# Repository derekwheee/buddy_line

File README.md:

# Line Buddy

A breadboard friend for prototyping with line level audio output

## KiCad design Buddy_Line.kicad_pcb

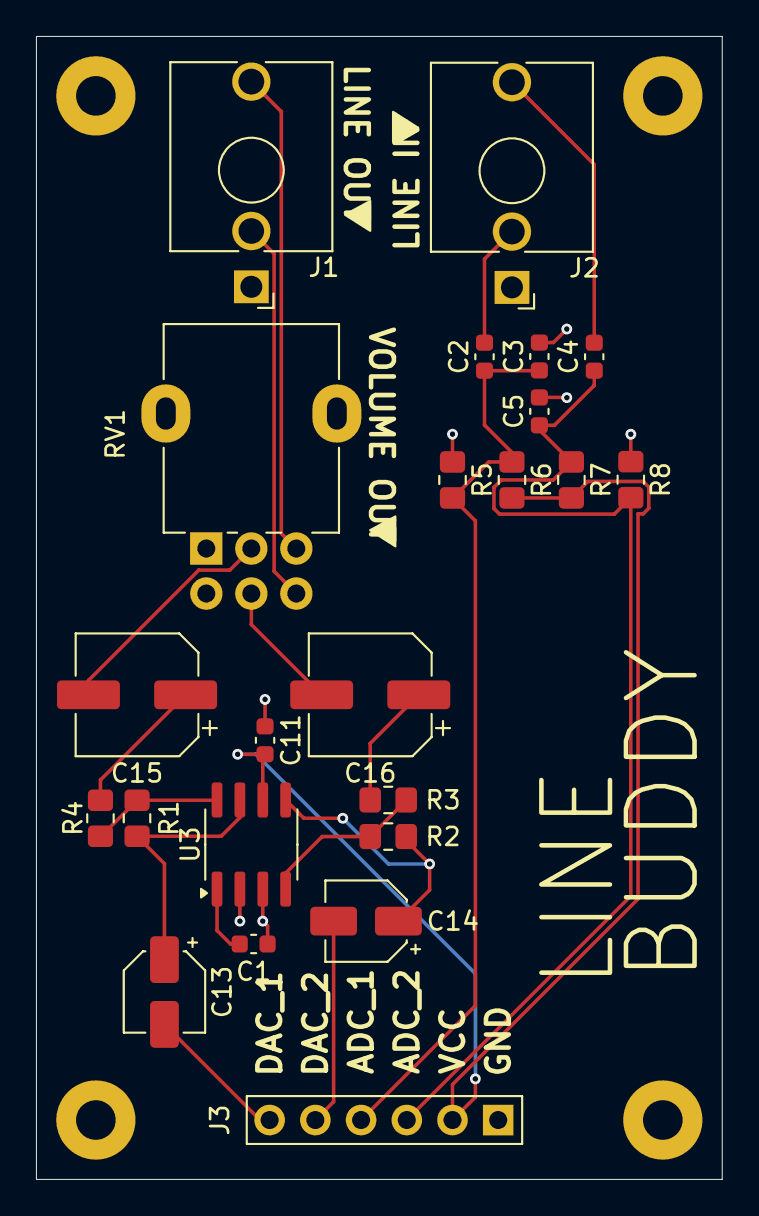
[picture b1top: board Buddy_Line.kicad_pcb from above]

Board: 2 copper layers, 38.1 x 63.5 mm, 27 parts (0 on the bottom side), 12 nets.

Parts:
C1, C3, C5, C11: 0.1u; C_0603_1608Metric
C2, C4: 10u; C_0603_1608Metric
C13, C14: 1u; CP_Elec_4x5.4
C15, C16: 68u; CP_Elec_6.3x7.7
H1, H2, H3, H4: MountingHole_Pad; MountingHole_2.2mm_M2_Pad
J1, J2: AudioJack3; Jack_3.5mm_QingPu_WQP-PJ398SM_Vertical_CircularHoles
J3: Conn_01x06_Pin; PinSocket_1x06_P2.54mm_Vertical
R1, R2: 33K; R_0805_2012Metric_Pad1.20x1.40mm_HandSolder
R3, R4: 22K; R_0805_2012Metric_Pad1.20x1.40mm_HandSolder
R5, R6, R7, R8: 1K; R_0805_2012Metric_Pad1.20x1.40mm_HandSolder
RV1: R_Potentiometer_Dual; Potentiometer_Alpha_RD902F-40-00D_Dual_Vertical
U3: TPA6110A2DGN; SOIC-8_3.9x4.9mm_P1.27mm

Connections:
+3.3V: C11.2, J3.5, R6.2, R7.2, U3.6 (VDD)
ADC_1: C2.1, C3.1, J3.3, R5.2, R6.1
ADC_2: C4.1, C5.1, J3.4, R7.1, R8.2
DAC_1: C13.2, J3.1
DAC_2: C14.2, J3.2
GND: C1.2, C3.2, C5.2, C11.1, H1.1, H2.1, H3.1, H4.1, J1.S, J2.S, J3.6, R5.1, R8.1, RV1.1, RV1.4, U3.2 (GND), U3.3 (SHDN)
unnamed: C2.2, J2.TN
unnamed: C4.2, J2.T
unnamed: J1.T, RV1.3
unnamed: J1.TN, RV1.6
unnamed: R1.2, R4.2, U3.8 (IN1-)
unnamed: R2.1, R3.2, U3.4 (IN2-)

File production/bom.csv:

Designator,Footprint,Quantity,Value,LCSC Part #
C1,0603,1,0.1u,
"C11, C3, C5",0603,3,0.1u,C6666325
"C13, C14",CP_Elec_4x5.4,2,1u,C3001203
"C15, C16",CP_Elec_6.3x7.7,2,68u,C5221836
"C2, C4",0603,2,10u,C6666325
"J1, J2",Jack_3.5mm_QingPu_WQP-PJ398SM_Vertical_CircularHoles,2,AudioJack3,
J3,PinSocket_1x06_P2.54mm_Vertical,1,Conn_01x06_Pin,
"R1, R2",0805,2,33K,
"R3, R4",0805,2,22K,
"R5, R6, R7, R8",0805,4,1K,
RV1,Potentiometer_Alpha_RD902F-40-00D_Dual_Vertical,1,R_Potentiometer_Dual,
U3,SOIC-8_3.9x4.9mm_P1.27mm,1,TPA6110A2DGN,C497472

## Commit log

2025-03-07 Update silkscreen
2025-03-08 New form factor
